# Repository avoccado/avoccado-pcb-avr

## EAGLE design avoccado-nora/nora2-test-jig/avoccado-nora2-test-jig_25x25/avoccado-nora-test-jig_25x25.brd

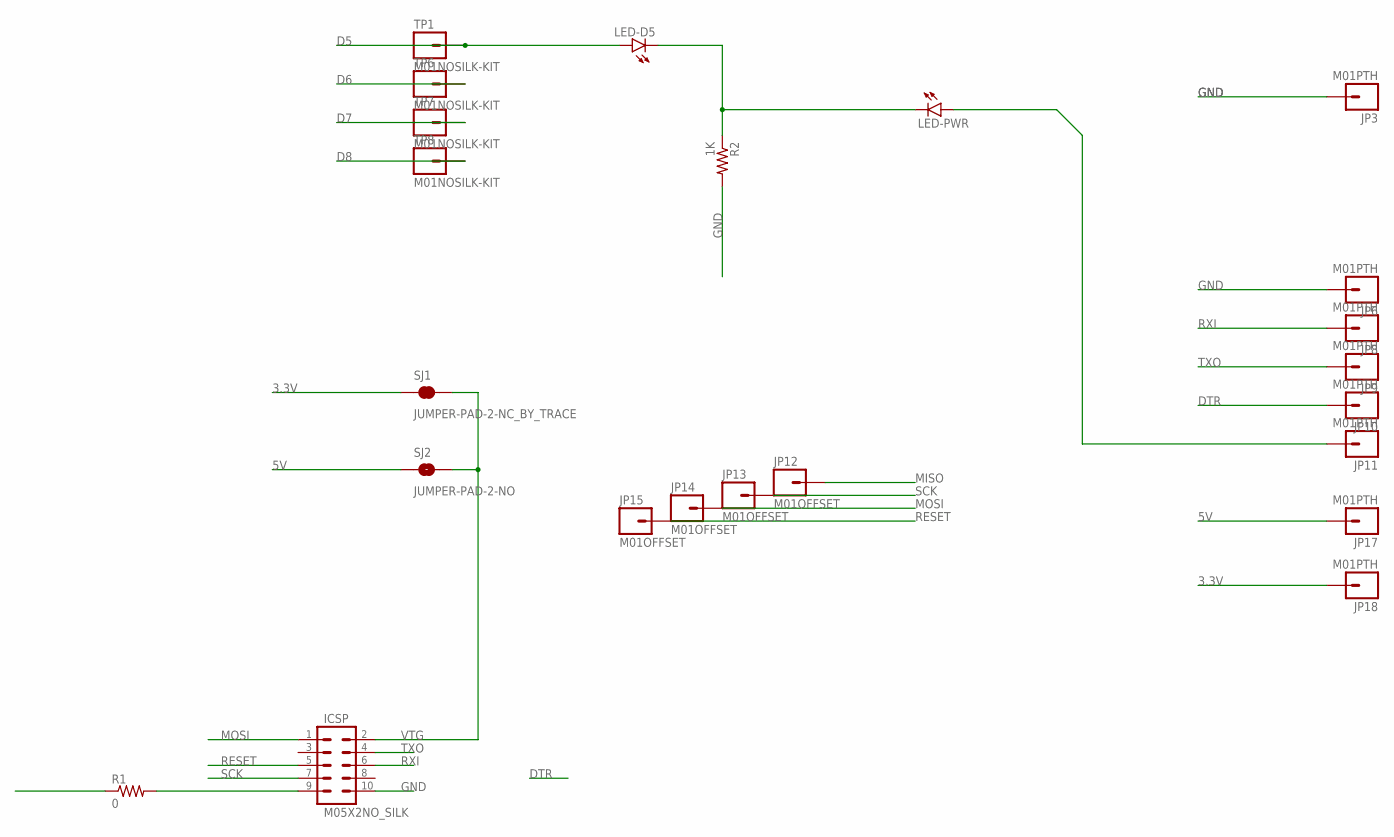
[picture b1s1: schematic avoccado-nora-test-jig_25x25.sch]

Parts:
ICSP: M05X2NO_SILK; 2X5_NOSILK
JP3, JP6, JP8, JP9, JP10, JP11, JP17, JP18: M01PTH; 1X01
JP12, JP13, JP14, JP15: M01OFFSET; 1X01_OFFSET
LED-D5: LED0603; LED-0603
LED-PWR: LED0603; LED-0603
R1: 0; 1206
R2: 1K; 0603-RES
SJ1: JUMPER-PAD-2-NC_BY_TRACE; PAD-JUMPER-2-NC_BY_TRACE_YES_SILK
SJ2: JUMPER-PAD-2-NO; PAD-JUMPER-2-NO_NO_SILK
TP1, TP6, TP7, TP8: M01NOSILK-KIT; 1X01NS-KIT

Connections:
3.3V: JP18.1, SJ1.1
5V: JP17.1, SJ2.1
D5: LED-D5.A, TP1.1
D6: TP6.1
D7: TP7.1
D8: TP8.1
DTR: JP10.1
GND: ICSP.10, JP3.1, JP6.1, R2.2
MISO: JP12.1, R1.1
MISO1: ICSP.9, R1.2
MOSI: ICSP.1, JP14.1
unnamed: LED-D5.C, LED-PWR.C, R2.1
unnamed: JP11.1, LED-PWR.A
RESET: ICSP.5, JP15.1
RXI: ICSP.6, JP8.1
SCK: ICSP.7, JP13.1
TXO: ICSP.4, JP9.1
VTG: ICSP.2, SJ1.2, SJ2.2

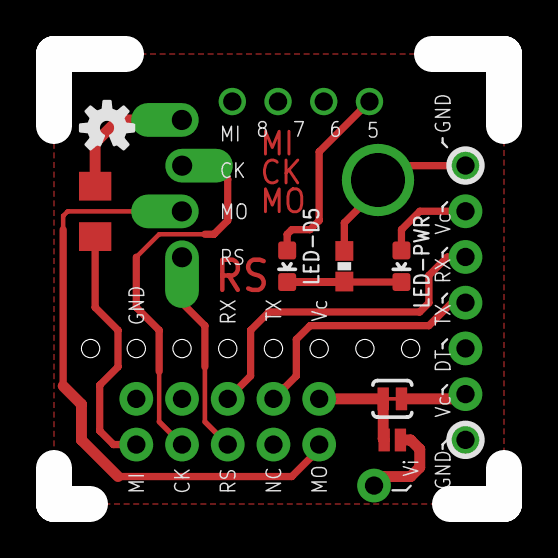
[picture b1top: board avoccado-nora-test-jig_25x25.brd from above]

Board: 2 copper layers, 25.0 x 25.0 mm, 24 parts (1 on the bottom side), 14 nets.

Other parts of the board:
LOGO2: OSHW-LOGOS; OSHW-LOGO-S

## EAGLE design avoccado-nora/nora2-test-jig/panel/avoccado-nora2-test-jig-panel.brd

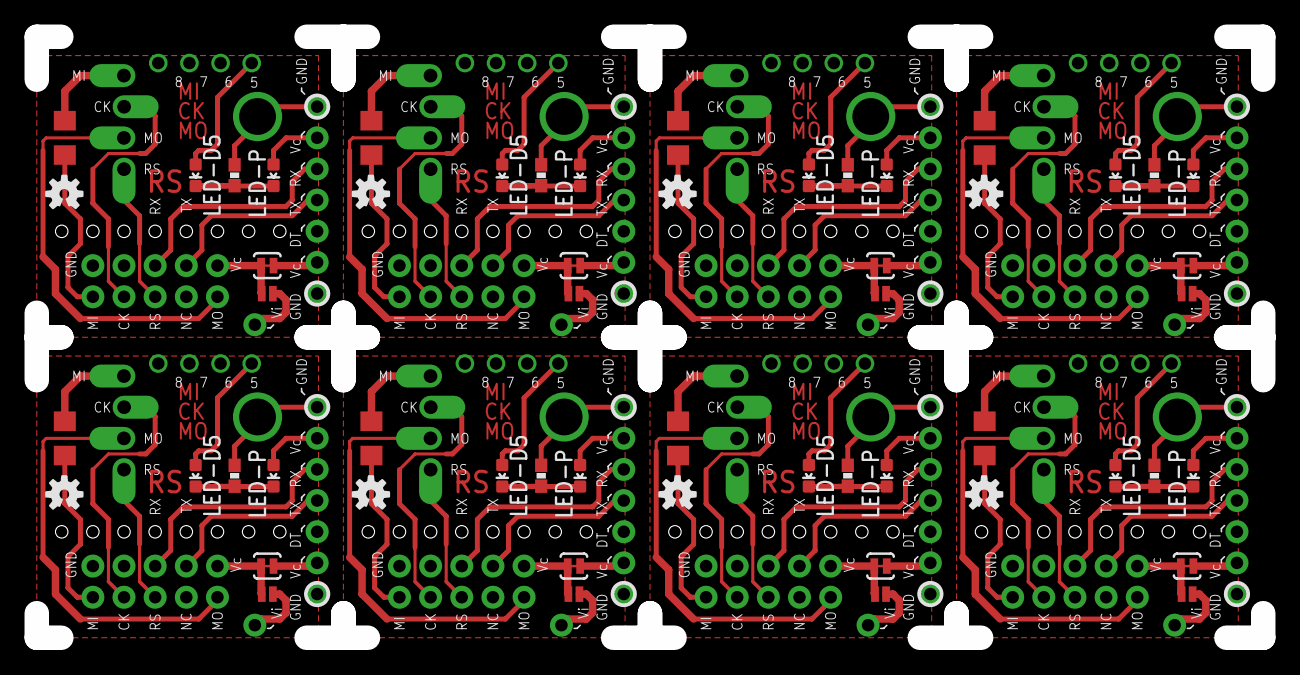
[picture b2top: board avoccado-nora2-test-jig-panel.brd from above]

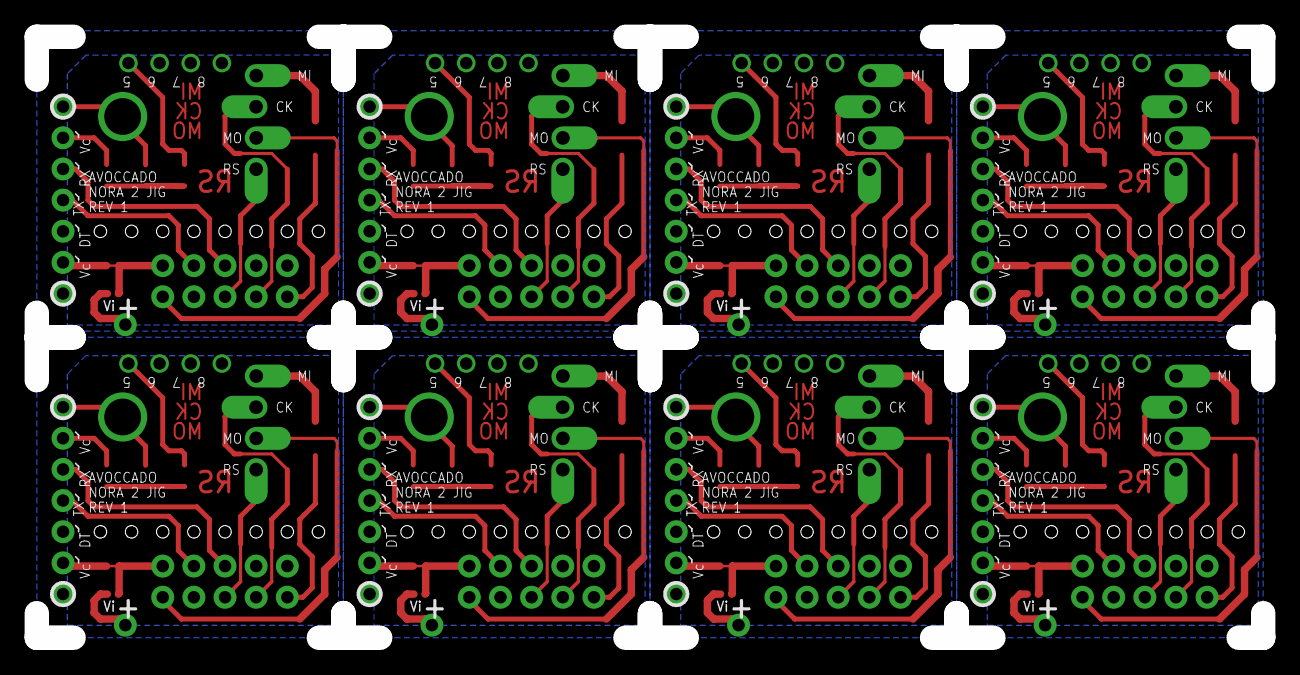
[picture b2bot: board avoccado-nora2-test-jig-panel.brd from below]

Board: 2 copper layers, 100.0 x 49.0 mm, 192 parts (8 on the bottom side), 112 nets.

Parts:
D5-LED, D5-LED1, D5-LED2, D5-LED3, D5-LED4, D5-LED5, D5-LED6, D5-LED7: LED-0603
ICSP, ICSP1, ICSP2, ICSP3, ICSP4, ICSP5, ICSP6, ICSP7: M05X2NO_SILK; 2X5_NOSILK
JP1, JP2, JP3, JP4, JP5, JP6, JP7, JP8, JP9, JP10, JP11, JP17, JP18, JP22, JP23, JP24, JP25, JP26, JP27, JP28, JP29, JP34, JP35, JP36, JP37, JP38, JP39, JP40, JP41, JP46, JP47, JP48, JP49, JP50, JP51, JP52, JP53, JP58, JP59, JP60, JP61, JP62, JP63, JP64, JP65, JP70, JP71, JP72, JP73, JP74, JP75, JP76, JP77, JP82, JP83, JP84, JP85, JP86, JP87, JP88, JP89, JP94, JP95, JP96: M01PTH; 1X01
JP12, JP13, JP14, JP15, JP16, JP19, JP20, JP21, JP30, JP31, JP32, JP33, JP42, JP43, JP44, JP45, JP54, JP55, JP56, JP57, JP66, JP67, JP68, JP69, JP78, JP79, JP80, JP81, JP90, JP91, JP92, JP93: M01OFFSET; 1X01_OFFSET
LOGO1, LOGO2, LOGO3, LOGO4, LOGO5, LOGO6, LOGO7, LOGO8: OSHW-LOGOS; OSHW-LOGO-S
PWR-LED, PWR-LED1, PWR-LED2, PWR-LED3, PWR-LED4, PWR-LED5, PWR-LED6, PWR-LED7: LED-0603
R1, R3, R5, R7, R9, R11, R13, R15: 0; 1206
R2, R4, R6, R8, R10, R12, R14, R16: 1K; 0603-RES
SJ1, SJ3, SJ5, SJ7, SJ9, SJ11, SJ13, SJ15: JUMPER-PAD-2-NC_BY_TRACE; PAD-JUMPER-2-NC_BY_TRACE_YES_SILK
SJ2, SJ4, SJ6, SJ8, SJ10, SJ12, SJ14, SJ16: JUMPER-PAD-2-NO; PAD-JUMPER-2-NO_NO_SILK
TP1, TP2, TP3, TP4, TP5, TP6, TP7, TP8, TP9, TP10, TP11, TP12, TP13, TP14, TP15, TP16, TP17, TP18, TP19, TP20, TP21, TP22, TP23, TP24, TP25, TP26, TP27, TP28, TP29, TP30, TP31, TP32: M01NOSILK-KIT; 1X01NS-KIT

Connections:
3.3V: JP18.1, SJ1.1
3.3V1: JP24.1, SJ3.1
3.3V2: JP36.1, SJ5.1
3.3V3: JP48.1, SJ7.1
3.3V4: JP60.1, SJ9.1
3.3V5: JP72.1, SJ11.1
3.3V6: JP84.1, SJ13.1
3.3V7: JP96.1, SJ15.1
5V: JP17.1, SJ2.1
5V1: JP23.1, SJ4.1
5V2: JP35.1, SJ6.1
5V3: JP47.1, SJ8.1
5V4: JP59.1, SJ10.1
5V5: JP71.1, SJ12.1
5V6: JP83.1, SJ14.1
5V7: JP95.1, SJ16.1
D2: D5-LED1.A, TP2.1
D5: D5-LED.A, TP1.1
D10: D5-LED2.A, TP9.1
D14: D5-LED3.A, TP13.1
D18: D5-LED4.A, TP17.1
D22: D5-LED5.A, TP21.1
D26: D5-LED6.A, TP25.1
D30: D5-LED7.A, TP29.1
GND: ICSP.10, JP3.1, JP6.1, R2.2
GND1: ICSP1.10, JP1.1, JP22.1, R4.2
GND2: ICSP2.10, JP25.1, JP34.1, R6.2
GND3: ICSP3.10, JP37.1, JP46.1, R8.2
GND4: ICSP4.10, JP49.1, JP58.1, R10.2
GND5: ICSP5.10, JP61.1, JP70.1, R12.2
GND6: ICSP6.10, JP73.1, JP82.1, R14.2
GND7: ICSP7.10, JP85.1, JP94.1, R16.2
MISO: JP12.1, R1.1
MISO1: ICSP.9, R1.2
MISO2: JP16.1, R3.1
MISO3: ICSP1.9, R3.2
MISO4: JP30.1, R5.1
MISO5: ICSP2.9, R5.2
MISO6: JP42.1, R7.1
MISO7: ICSP3.9, R7.2
MISO8: JP54.1, R9.1
MISO9: ICSP4.9, R9.2
MISO10: JP66.1, R11.1
MISO11: ICSP5.9, R11.2
MISO12: JP78.1, R13.1
MISO13: ICSP6.9, R13.2
MISO14: JP90.1, R15.1
MISO15: ICSP7.9, R15.2
MOSI: ICSP.1, JP14.1
MOSI1: ICSP1.1, JP20.1
MOSI2: ICSP2.1, JP32.1
MOSI3: ICSP3.1, JP44.1
MOSI4: ICSP4.1, JP56.1
MOSI5: ICSP5.1, JP68.1
MOSI6: ICSP6.1, JP80.1
MOSI7: ICSP7.1, JP92.1
unnamed: D5-LED.C, PWR-LED.C, R2.1
unnamed: JP11.1, PWR-LED.A
unnamed: D5-LED1.C, PWR-LED1.C, R4.1
unnamed: JP7.1, PWR-LED1.A
unnamed: D5-LED2.C, PWR-LED2.C, R6.1
unnamed: JP29.1, PWR-LED2.A
unnamed: D5-LED3.C, PWR-LED3.C, R8.1
unnamed: JP41.1, PWR-LED3.A
unnamed: D5-LED4.C, PWR-LED4.C, R10.1
unnamed: JP53.1, PWR-LED4.A
unnamed: D5-LED5.C, PWR-LED5.C, R12.1
unnamed: JP65.1, PWR-LED5.A
unnamed: D5-LED6.C, PWR-LED6.C, R14.1
unnamed: JP77.1, PWR-LED6.A
unnamed: D5-LED7.C, PWR-LED7.C, R16.1
unnamed: JP89.1, PWR-LED7.A
RESET: ICSP.5, JP15.1
RESET1: ICSP1.5, JP21.1
RESET2: ICSP2.5, JP33.1
RESET3: ICSP3.5, JP45.1
RESET4: ICSP4.5, JP57.1
RESET5: ICSP5.5, JP69.1
RESET6: ICSP6.5, JP81.1
RESET7: ICSP7.5, JP93.1
RXI: ICSP.6, JP8.1
RXI1: ICSP1.6, JP2.1
RXI2: ICSP2.6, JP26.1
RXI3: ICSP3.6, JP38.1
RXI4: ICSP4.6, JP50.1
RXI5: ICSP5.6, JP62.1
RXI6: ICSP6.6, JP74.1
RXI7: ICSP7.6, JP86.1
SCK: ICSP.7, JP13.1
SCK1: ICSP1.7, JP19.1
SCK2: ICSP2.7, JP31.1
SCK3: ICSP3.7, JP43.1
SCK4: ICSP4.7, JP55.1
SCK5: ICSP5.7, JP67.1
SCK6: ICSP6.7, JP79.1
SCK7: ICSP7.7, JP91.1
TXO: ICSP.4, JP9.1
TXO1: ICSP1.4, JP4.1
TXO2: ICSP2.4, JP27.1
TXO3: ICSP3.4, JP39.1
TXO4: ICSP4.4, JP51.1
TXO5: ICSP5.4, JP63.1
TXO6: ICSP6.4, JP75.1
TXO7: ICSP7.4, JP87.1
VTG: ICSP.2, SJ1.2, SJ2.2
VTG1: ICSP1.2, SJ3.2, SJ4.2
VTG2: ICSP2.2, SJ5.2, SJ6.2
VTG3: ICSP3.2, SJ7.2, SJ8.2
VTG4: ICSP4.2, SJ9.2, SJ10.2
VTG5: ICSP5.2, SJ11.2, SJ12.2
VTG6: ICSP6.2, SJ13.2, SJ14.2
VTG7: ICSP7.2, SJ15.2, SJ16.2

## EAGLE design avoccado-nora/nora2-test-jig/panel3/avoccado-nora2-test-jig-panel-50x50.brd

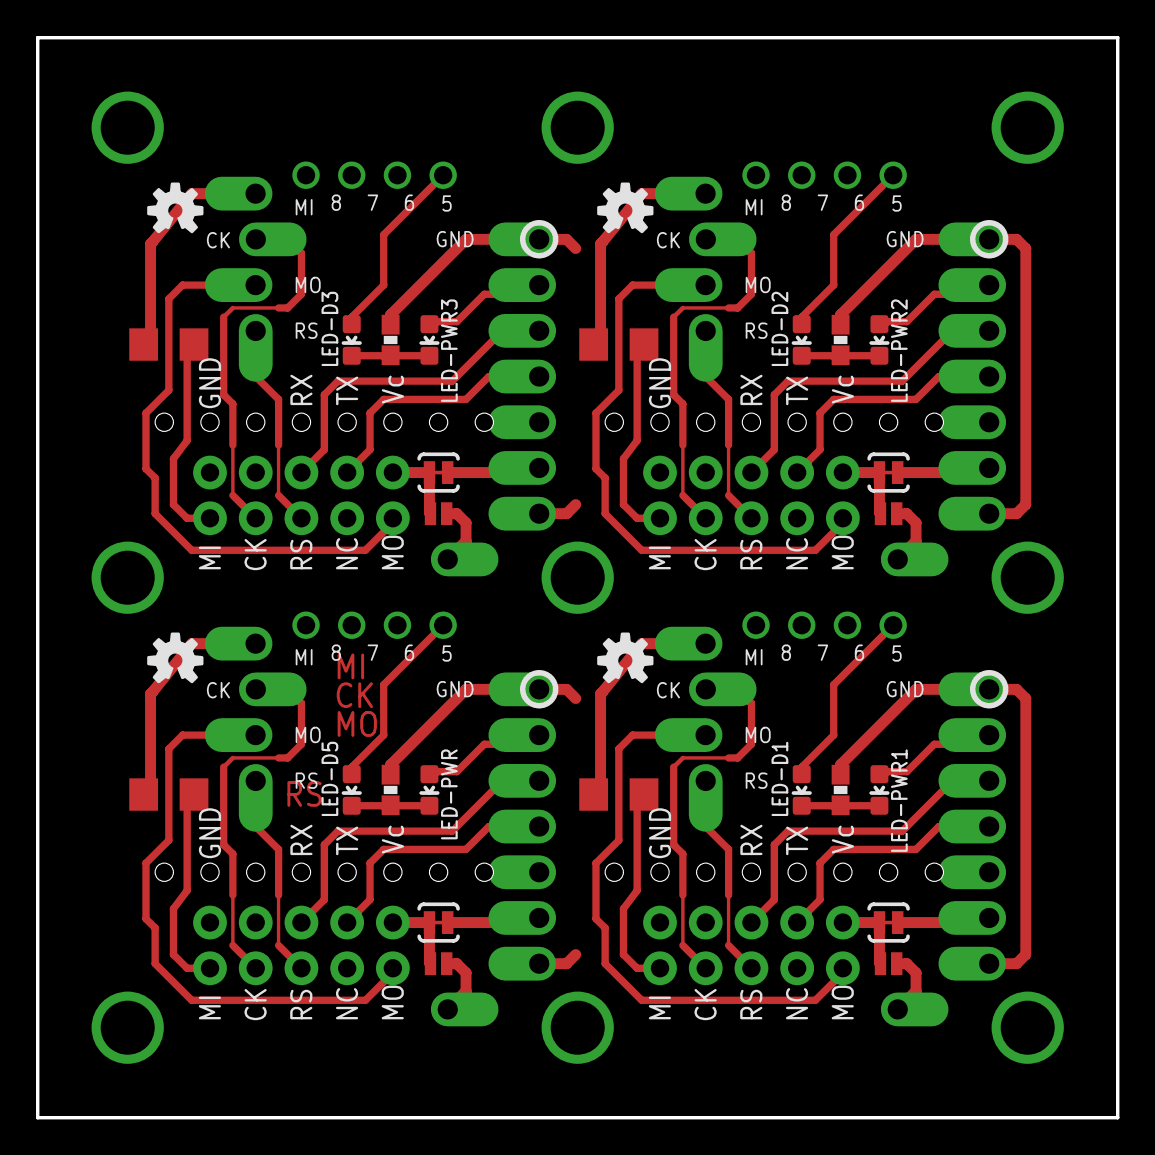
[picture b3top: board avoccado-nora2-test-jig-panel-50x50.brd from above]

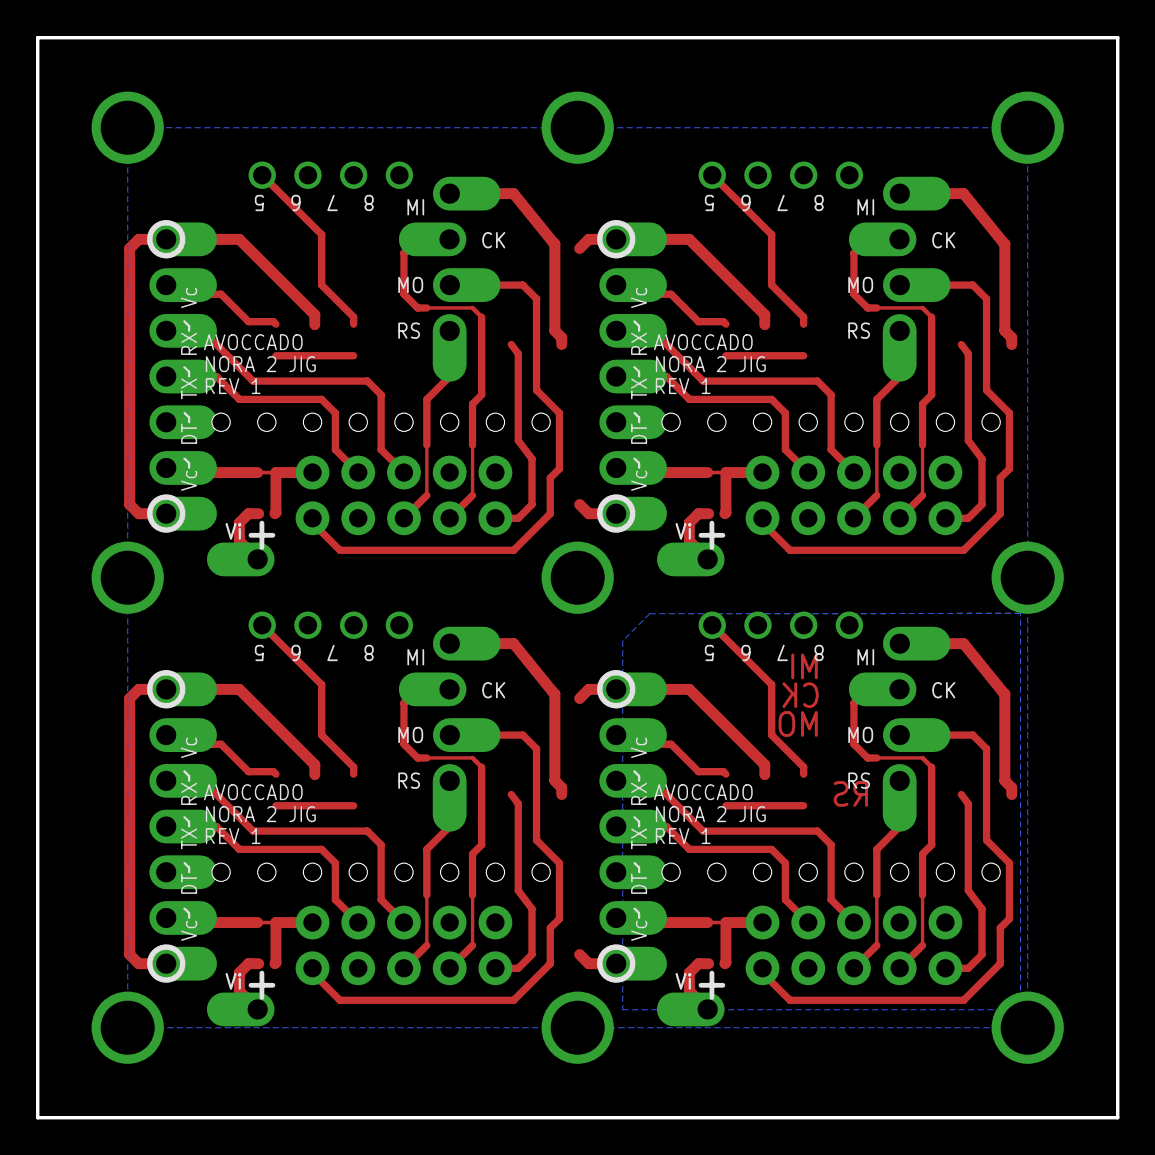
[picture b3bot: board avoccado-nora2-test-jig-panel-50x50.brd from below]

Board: 2 copper layers, 60.0 x 60.0 mm, 96 parts (4 on the bottom side), 53 nets.

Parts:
ICSP, ICSP1, ICSP2, ICSP3: M05X2NO_SILK; 2X5_NOSILK
JP1, JP2, JP3, JP4, JP5, JP6, JP7, JP8, JP9, JP10, JP11, JP12, JP13, JP14, JP15, JP16, JP17, JP18, JP19, JP20, JP21, JP22, JP23, JP24, JP25, JP26, JP27, JP28, JP29, JP30, JP31, JP32, JP33, JP34, JP35, JP36, JP37, JP38, JP39, JP40, JP41, JP42, JP43, JP44, JP45, JP46, JP47, JP48: M01OFFSET; 1X01_OFFSET
LED-D1, LED-D2, LED-D3, LED-D5: LED-0603
LED-PWR, LED-PWR1, LED-PWR2, LED-PWR3: LED-0603
LOGO1, LOGO2, LOGO3, LOGO4: OSHW-LOGOS; OSHW-LOGO-S
R1, R3, R5, R7: 0; 1206
R2, R4, R6, R8: 1K; 0603-RES
SJ1, SJ3, SJ5, SJ7: JUMPER-PAD-2-NC_BY_TRACE; PAD-JUMPER-2-NC_BY_TRACE_YES_SILK
SJ2, SJ4, SJ6, SJ8: JUMPER-PAD-2-NO; PAD-JUMPER-2-NO_NO_SILK
TP1, TP2, TP3, TP4, TP5, TP6, TP7, TP8, TP9, TP10, TP11, TP12, TP13, TP14, TP15, TP16: M01NOSILK-KIT; 1X01NS-KIT

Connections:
3.3V: JP19.1, SJ1.1
3.3V1: JP23.1, SJ3.1
3.3V2: JP35.1, SJ5.1
3.3V3: JP47.1, SJ7.1
5V: JP16.1, SJ2.1
5V1: JP22.1, SJ4.1
5V2: JP34.1, SJ6.1
5V3: JP46.1, SJ8.1
D2: LED-D1.A, TP2.1
D5: LED-D5.A, TP1.1
D10: LED-D2.A, TP9.1
D14: LED-D3.A, TP13.1
GND: ICSP.10, ICSP1.10, ICSP2.10, ICSP3.10, JP1.1, JP10.1, JP20.1, JP24.1, JP29.1, JP36.1, JP41.1, JP48.1, R2.2, R4.2, R6.2, R8.2
MISO: JP12.1, R1.1
MISO1: ICSP.9, R1.2
MISO2: JP3.1, R3.1
MISO3: ICSP1.9, R3.2
MISO4: JP25.1, R5.1
MISO5: ICSP2.9, R5.2
MISO6: JP37.1, R7.1
MISO7: ICSP3.9, R7.2
MOSI: ICSP.1, JP14.1
MOSI1: ICSP1.1, JP8.1
MOSI2: ICSP2.1, JP27.1
MOSI3: ICSP3.1, JP39.1
unnamed: LED-D5.C, LED-PWR.C, R2.1
unnamed: JP7.1, LED-PWR.A
unnamed: LED-D1.C, LED-PWR1.C, R4.1
unnamed: JP21.1, LED-PWR1.A
unnamed: LED-D2.C, LED-PWR2.C, R6.1
unnamed: JP33.1, LED-PWR2.A
unnamed: LED-D3.C, LED-PWR3.C, R8.1
unnamed: JP45.1, LED-PWR3.A
RESET: ICSP.5, JP15.1
RESET1: ICSP1.5, JP9.1
RESET2: ICSP2.5, JP28.1
RESET3: ICSP3.5, JP40.1
RXI: ICSP.6, JP2.1
RXI1: ICSP1.6, JP11.1
RXI2: ICSP2.6, JP30.1
RXI3: ICSP3.6, JP42.1
SCK: ICSP.7, JP13.1
SCK1: ICSP1.7, JP6.1
SCK2: ICSP2.7, JP26.1
SCK3: ICSP3.7, JP38.1
TXO: ICSP.4, JP4.1
TXO1: ICSP1.4, JP17.1
TXO2: ICSP2.4, JP31.1
TXO3: ICSP3.4, JP43.1
VTG: ICSP.2, SJ1.2, SJ2.2
VTG1: ICSP1.2, SJ3.2, SJ4.2
VTG2: ICSP2.2, SJ5.2, SJ6.2
VTG3: ICSP3.2, SJ7.2, SJ8.2

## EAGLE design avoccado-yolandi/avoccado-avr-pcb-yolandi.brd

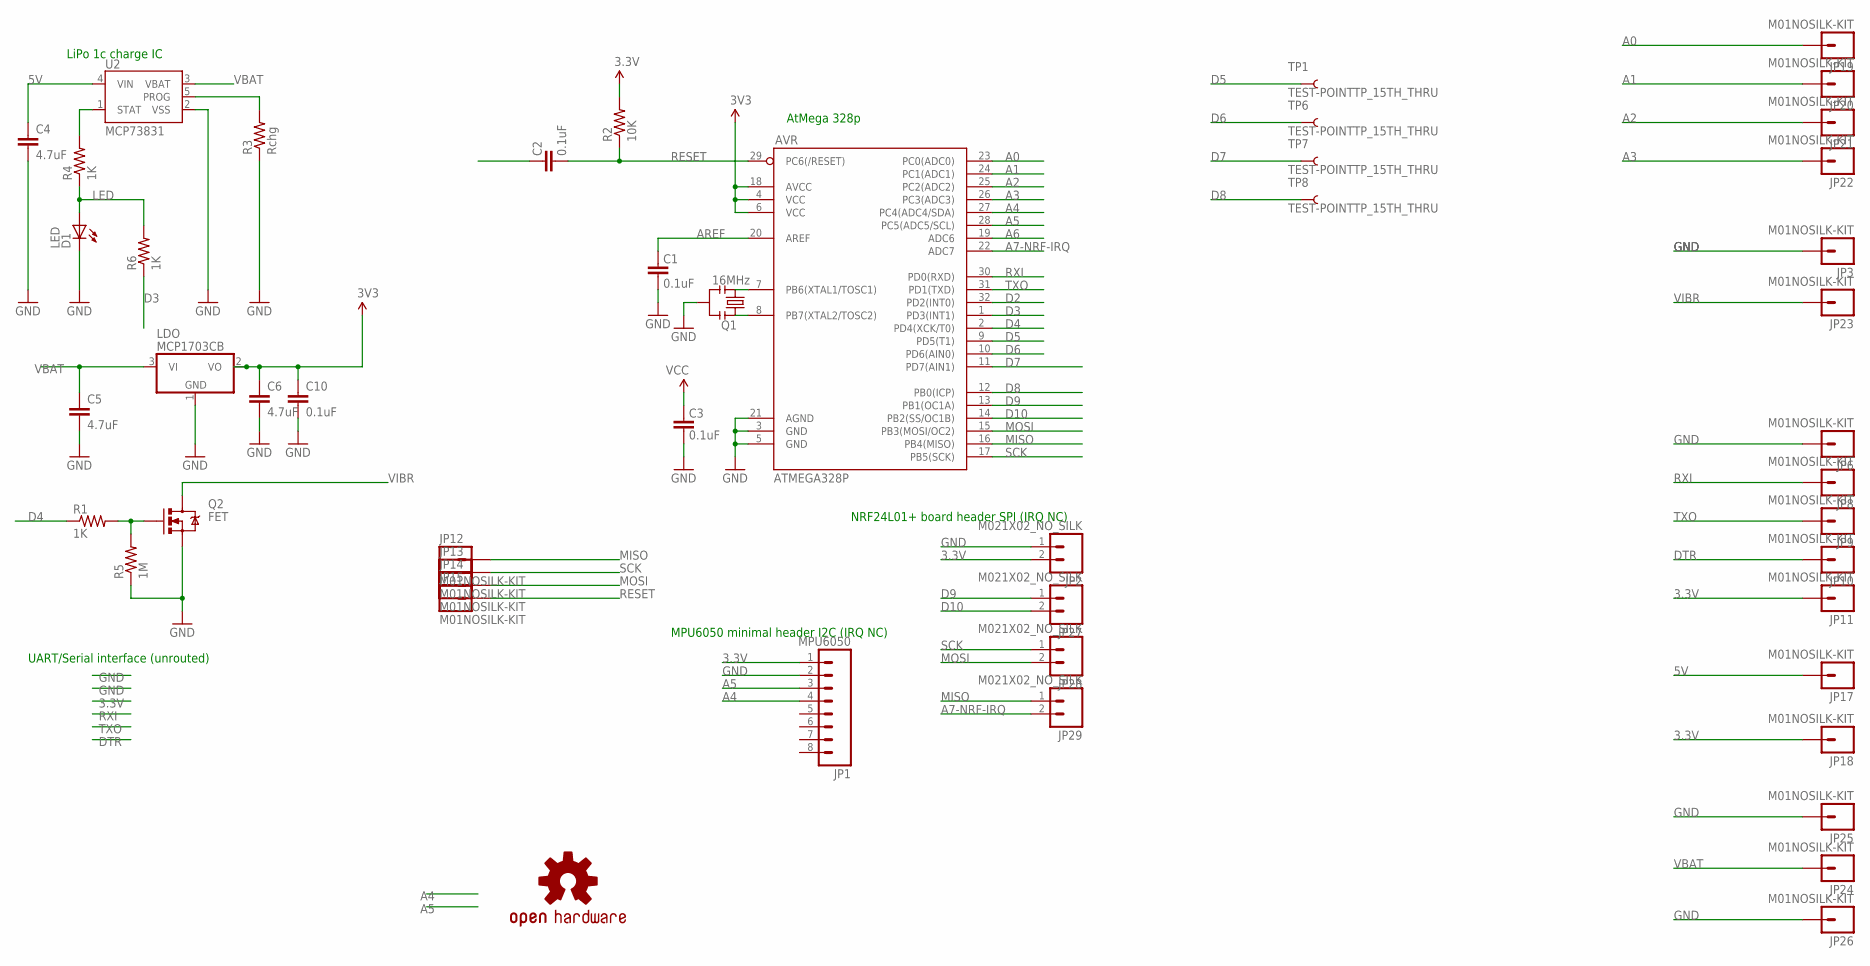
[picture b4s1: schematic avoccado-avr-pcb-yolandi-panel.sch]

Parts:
AVR: ATMEGA328P; TQFP32-08
C1, C2, C3, C10: 0.1uF; C0402
C4, C5, C6: 4.7uF; 0603-CAP
D1: LED; LED-0603
JP1: MPU6050; 1X08_PIN1_NO_SILK
JP2, JP27, JP28, JP29: M021X02_NO_SILK; 1X02_NO_SILK
JP3, JP6, JP8, JP9, JP10, JP11, JP12, JP13, JP14, JP15, JP17, JP18, JP19, JP20, JP21, JP22, JP23, JP24, JP25, JP26: M01NOSILK-KIT; 1X01NS-KIT
LDO: MCP1703CB; SOT23
LOGO1: OSHW-LOGOS; OSHW-LOGO-S
Q1: 16MHz; RESONATOR-SMD
Q2: FET; SOT323
R1, R4, R6: 1K; 0603-RES
R2: 10K; 0603-RES
R3: Rchg; 0603-RES
R5: 1M; 0603-RES
TP1, TP6, TP7, TP8: TEST-POINTTP_15TH_THRU; TP_15TH
U2: MCP73831; SOT23-5

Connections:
3.3V: AVR.4 (VCC), AVR.6 (VCC), AVR.18 (AVCC), C3.2, C6.1, C10.1, JP1.1, JP2.2, JP11.1, JP18.1, LDO.2 (VO), R2.2
5V: C4.1, JP17.1, U2.4 (VIN)
A0: AVR.23 (PC0(ADC0)), JP19.1
A1: AVR.24 (PC1(ADC1)), JP20.1
A2: AVR.25 (PC2(ADC2)), JP21.1
A3: AVR.26 (PC3(ADC3)), JP22.1
A4: AVR.27 (PC4(ADC4/SDA)), JP1.4
A5: AVR.28 (PC5(ADC5/SCL)), JP1.3
A6: AVR.19 (ADC6)
A7-NRF-IRQ: AVR.22 (ADC7), JP29.2
AREF: AVR.20 (AREF), C1.2
CHG-PROG: R3.2, U2.5 (PROG)
D2: AVR.32 (PD2(INT0))
D3: AVR.1 (PD3(INT1)), R6.1
D4: AVR.2 (PD4(XCK/T0)), R1.1
D5: AVR.9 (PD5(T1)), TP1.P$1
D6: AVR.10 (PD6(AIN0)), TP6.P$1
D7: AVR.11 (PD7(AIN1)), TP7.P$1
D8: AVR.12 (PB0(ICP)), TP8.P$1
D9: AVR.13 (PB1(OC1A)), JP27.1
D10: AVR.14 (PB2(SS/OC1B)), JP27.2
DTR: C2.2, JP10.1
GND: AVR.3 (GND), AVR.5 (GND), AVR.21 (AGND), C1.1, C3.1, C4.2, C5.2, C6.2, C10.2, D1.C, JP1.2, JP2.1, JP3.1, JP6.1, JP25.1, JP26.1, LDO.1 (GND), Q1.2, Q2.2 (S), R3.1, R5.1, U2.2 (VSS)
LED: D1.A, R4.1, R6.2
MISO: AVR.16 (PB4(MISO)), JP12.1, JP29.1
MOSI: AVR.15 (PB3(MOSI/OC2)), JP14.1, JP28.2
unnamed: AVR.8 (PB7(XTAL2/TOSC2)), Q1.1
unnamed: AVR.7 (PB6(XTAL1/TOSC1)), Q1.3
unnamed: Q2.1 (G), R1.2, R5.2
RESET: AVR.29 (PC6(/RESET)), C2.1, JP15.1, R2.1
RXI: AVR.30 (PD0(RXD)), JP8.1
SCK: AVR.17 (PB5(SCK)), JP13.1, JP28.1
SOC: R4.2, U2.1 (STAT)
TXO: AVR.31 (PD1(TXD)), JP9.1
VBAT: C5.1, JP24.1, LDO.3 (VI), U2.3 (VBAT)
VIBR: JP23.1, Q2.3 (D)

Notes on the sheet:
NRF24L01+ board header SPI (IRQ NC)
MPU6050 minimal header I2C (IRQ NC)
AtMega 328p
LiPo 1c charge IC
UART/Serial interface (unrouted)

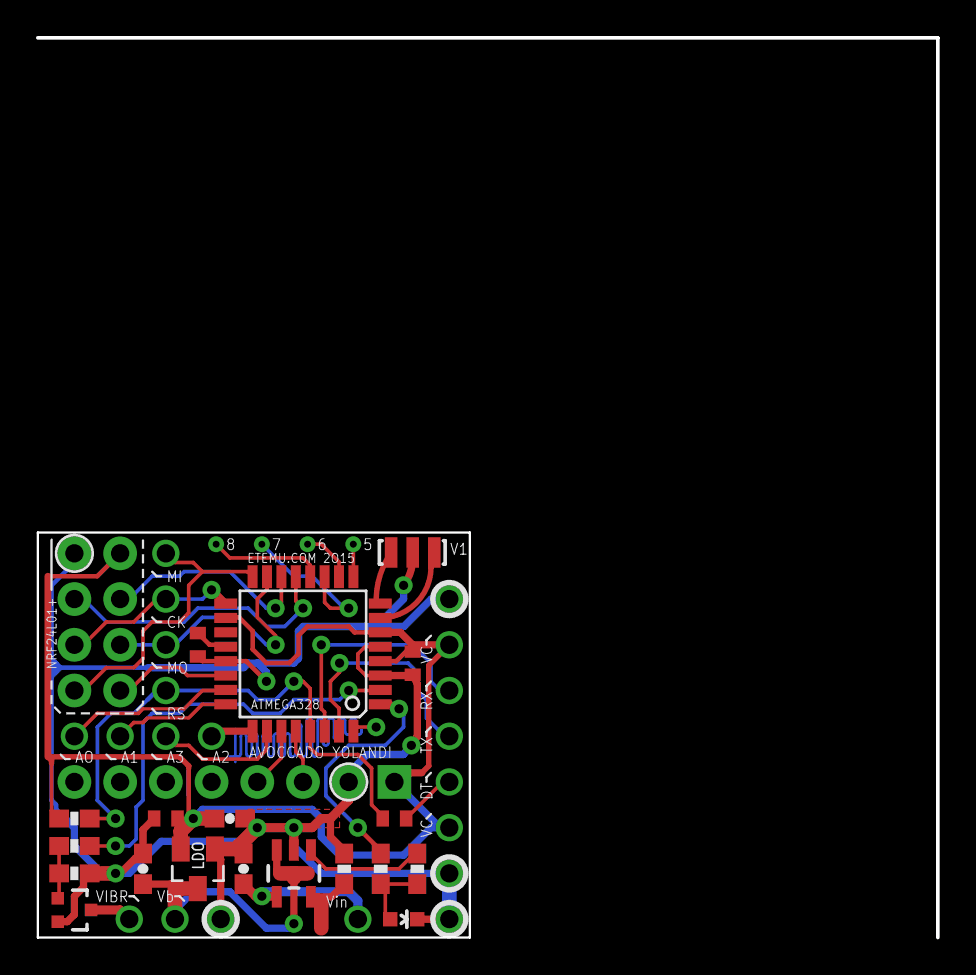
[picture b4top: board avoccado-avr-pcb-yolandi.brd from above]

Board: 2 copper layers, 24.0 x 22.5 mm, 49 parts (1 on the bottom side), 34 nets.

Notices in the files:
parts and their libraries:
SparkFun-Connectors: Licensing: Creative Commons ShareAlike 4.0 International - https://creativecommons.org/licenses/by-sa/4.0
